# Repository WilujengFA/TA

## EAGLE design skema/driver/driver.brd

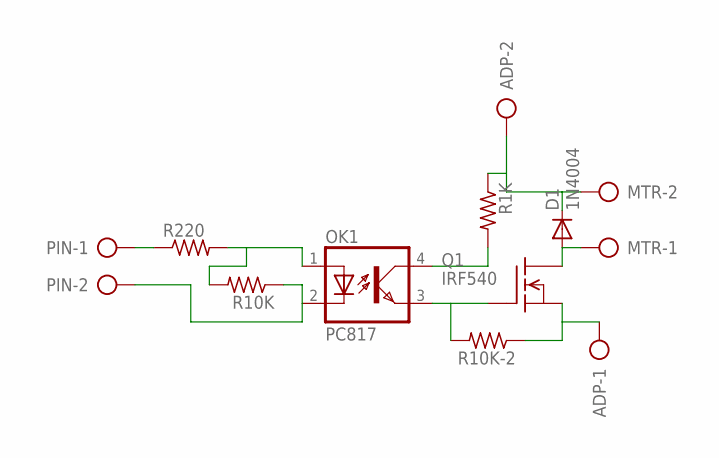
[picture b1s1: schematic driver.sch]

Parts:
ADP: AK300/2
D1: 1N4004; DO41-10
MTR: AK300/2
OK1: PC817; DIL04
PIN: AK300/2
Q1: IRF540; TO220
R1K, R10K, R10K-2, R220: R-US_0204/7; 0204/7

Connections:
unnamed: OK1.1 (A), R10K.2, R220.2
unnamed: ADP.1, Q1.3 (S), R10K-2.1
unnamed: D1.A, MTR.1, Q1.2 (D)
unnamed: OK1.3 (EMIT), Q1.1 (G), R10K-2.2
unnamed: OK1.4 (COL), R1K.2
unnamed: PIN.1, R220.1
unnamed: ADP.2, D1.C, MTR.2, R1K.1
unnamed: OK1.2 (C), PIN.2, R10K.1

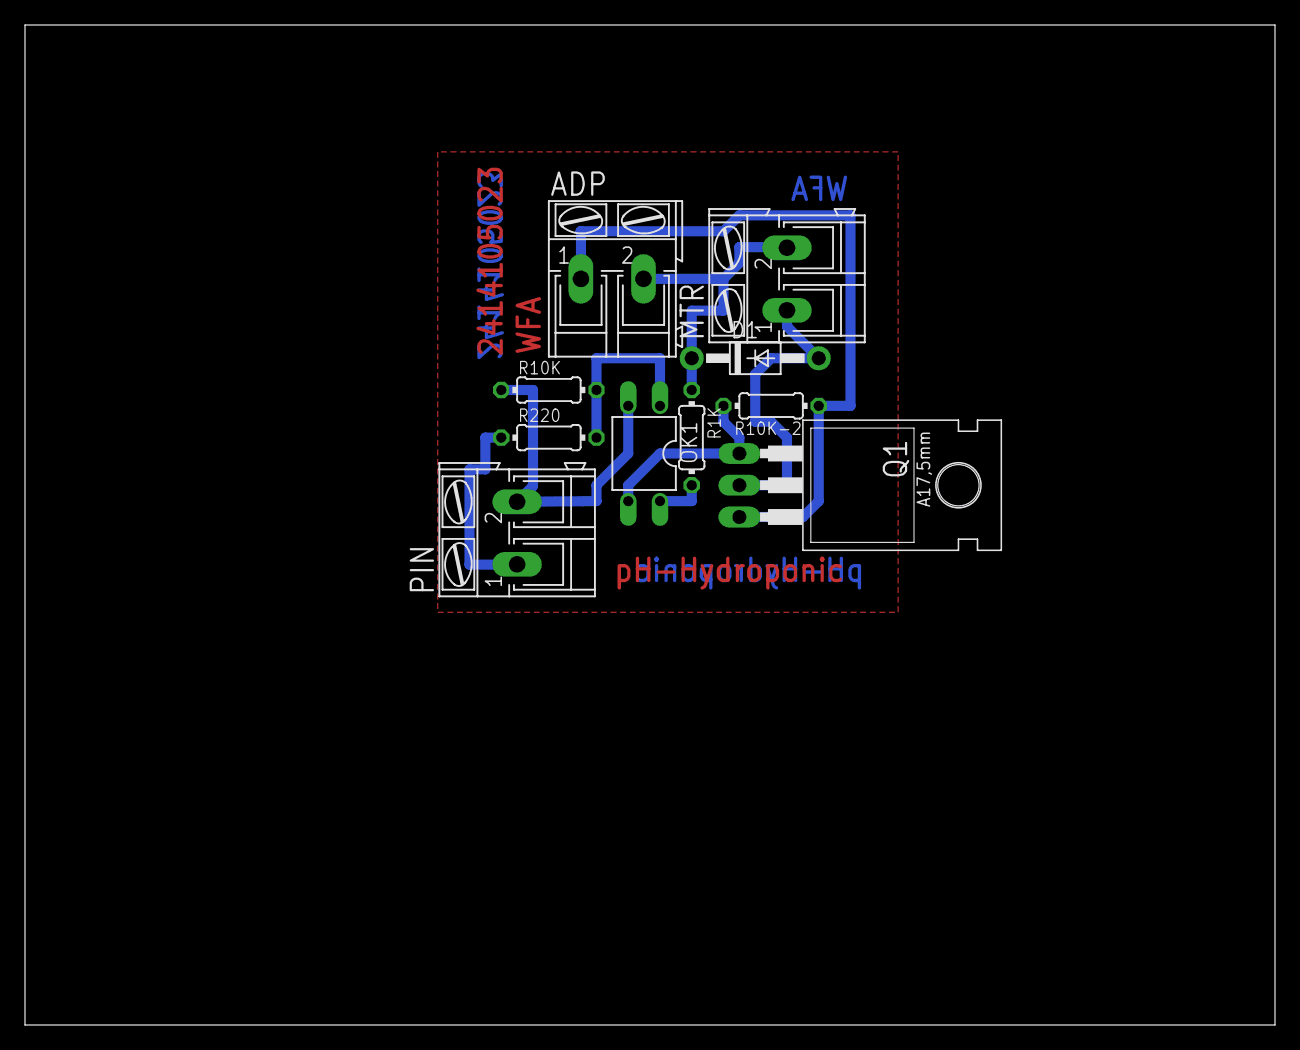
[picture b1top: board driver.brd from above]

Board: 2 copper layers, 100.0 x 80.0 mm, 10 parts (0 on the bottom side), 8 nets.

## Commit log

2016-05-01 mulai
2016-05-01 nilai statis
2016-05-01 data upload
2016-05-01 driver
2016-05-01 pwm oke
2016-06-01 Create kodingsensor
2016-06-02 bismillah
